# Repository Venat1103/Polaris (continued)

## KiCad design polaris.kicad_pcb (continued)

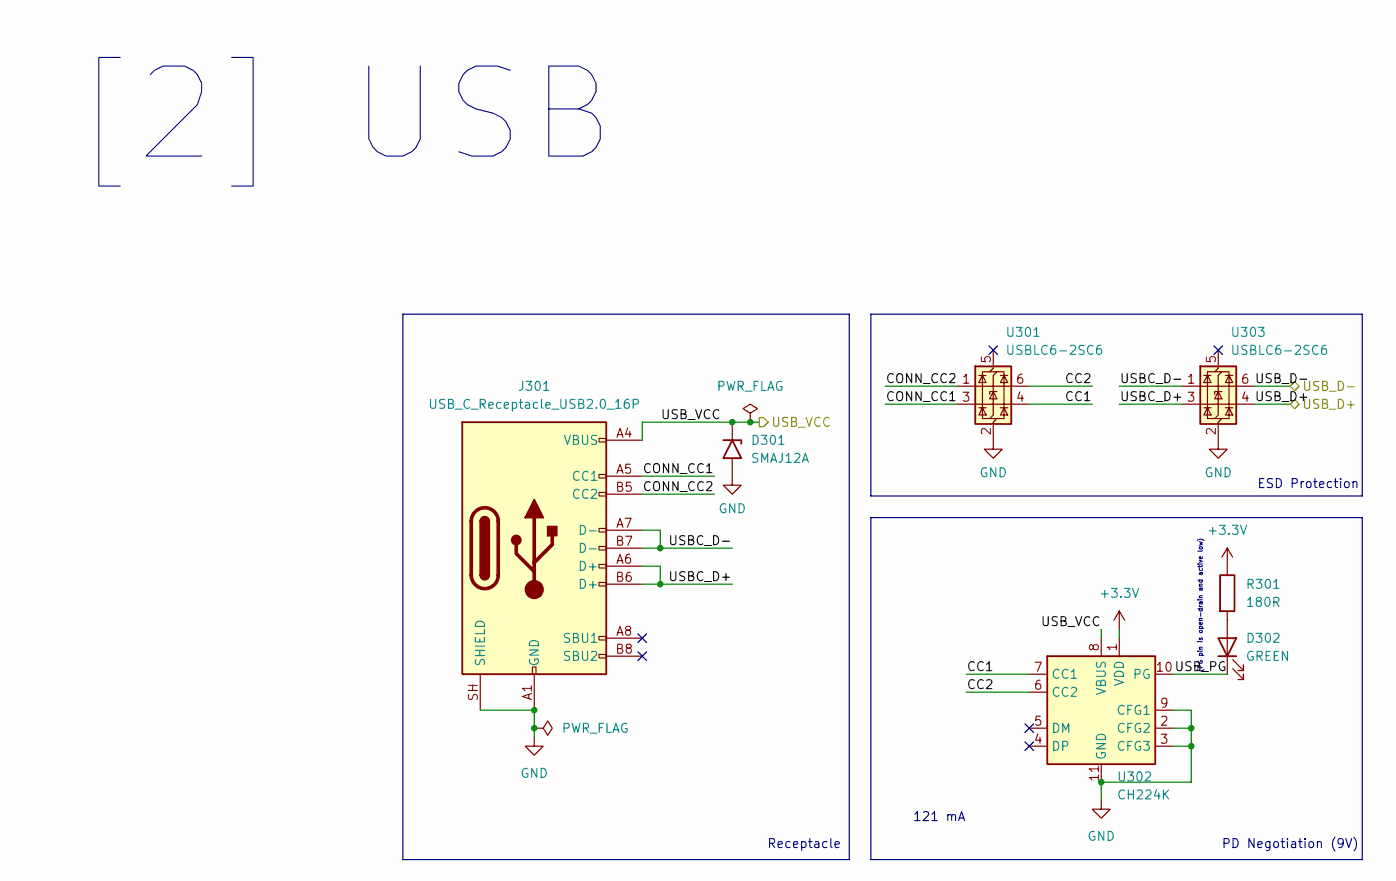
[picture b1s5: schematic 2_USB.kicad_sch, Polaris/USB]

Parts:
D301: SMAJ12A; D_SMA
D302: GREEN; LED_0603_1608Metric
J301: USB_C_Receptacle_USB2.0_16P; USB_C_Receptacle_HRO_TYPE-C-31-M-12
R301: 180R; R_0603_1608Metric
U301, U303: USBLC6-2SC6; SOT-23-6
U302: CH224K; SSOP-10-1EP_3.9x4.9mm_P1mm_EP2.1x3.3mm

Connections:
+3.3V: R301.1, U302.1 (VDD); also elsewhere on the board
/1_Power/USB_VCC: D301.1 (A1), J301.A4 (VBUS), J301.A9 (VBUS), J301.B4 (VBUS), J301.B9 (VBUS), U302.8 (VBUS); also elsewhere on the board
/2_USB/CC1: U301.4 (I/O2), U302.7 (CC1)
/2_USB/CC2: U301.6 (I/O1), U302.6 (CC2)
/2_USB/CONN_CC1: J301.A5 (CC1), U301.3 (I/O2)
/2_USB/CONN_CC2: J301.B5 (CC2), U301.1 (I/O1)
/2_USB/USBC_D+: J301.A6 (D+), J301.B6 (D+), U303.3 (I/O2)
/2_USB/USBC_D-: J301.A7 (D-), J301.B7 (D-), U303.1 (I/O1)
/2_USB/USB_D+: U303.4 (I/O2); also elsewhere on the board
/2_USB/USB_D-: U303.6 (I/O1); also elsewhere on the board
/2_USB/USB_PG: D302.1 (K), U302.10 (PG)
GND: D301.2 (A2), J301.A1 (GND), J301.A12 (GND), J301.B1 (GND), J301.B12 (GND), J301.SH (SHIELD), U301.2 (GND), U302.2 (CFG2), U302.3 (CFG3), U302.9 (CFG1), U302.11 (GND), U303.2 (GND); also elsewhere on the board
unnamed: D302.2 (A), R301.2

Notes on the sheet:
(PG pin is open-drain and active low)
Receptacle
[2] USB
121 mA
ESD Protection
PD Negotiation (9V)

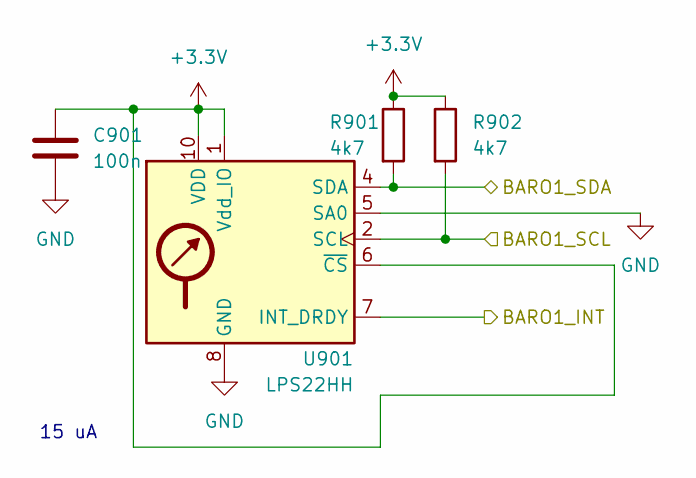
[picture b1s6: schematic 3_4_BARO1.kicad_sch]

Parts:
C901: 100n; C_0603_1608Metric
R901, R902: 4k7; R_0603_1608Metric
U901: LPS22HH; ST_HLGA-10_2x2mm_P0.5mm_LayoutBorder3x2y

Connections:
+3.3V: C901.2, R901.1, R902.1, U901.1 (Vdd_IO), U901.6 (~CS), U901.10 (VDD); also elsewhere on the board
/3_NavigationProcessor/LPS_INT: U901.7 (INT_DRDY); also elsewhere on the board
/3_NavigationProcessor/LPS_SCL: R902.2, U901.2 (SCL); also elsewhere on the board
/3_NavigationProcessor/LPS_SDA: R901.2, U901.4 (SDA); also elsewhere on the board
GND: C901.1, U901.3 (GND), U901.5 (SA0), U901.8 (GND), U901.9 (GND); also elsewhere on the board

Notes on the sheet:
15 uA

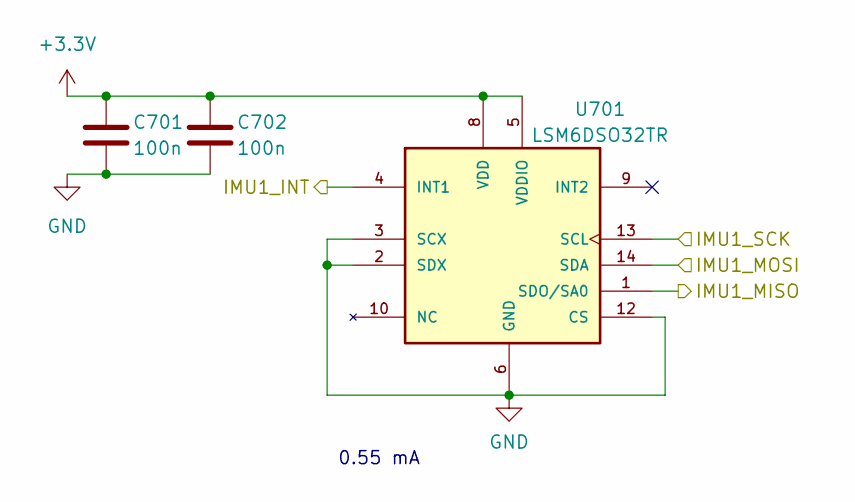
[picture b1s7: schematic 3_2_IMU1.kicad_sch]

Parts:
C701, C702: 100n; C_0603_1608Metric
U701: LSM6DSO32TR

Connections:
+3.3V: C701.1, C702.1, U701.5 (VDDIO), U701.8 (VDD); also elsewhere on the board
/3_NavigationProcessor/LSM_INT: U701.4 (INT1); also elsewhere on the board
/3_NavigationProcessor/LSM_MISO: U701.1 (SDO/SA0); also elsewhere on the board
/3_NavigationProcessor/LSM_MOSI: U701.14 (SDA); also elsewhere on the board
/3_NavigationProcessor/LSM_SCK: U701.13 (SCL); also elsewhere on the board
GND: C701.2, C702.2, U701.2 (SDX), U701.3 (SCX), U701.6 (GND), U701.7 (GND), U701.12 (CS); also elsewhere on the board

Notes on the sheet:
0.55 mA

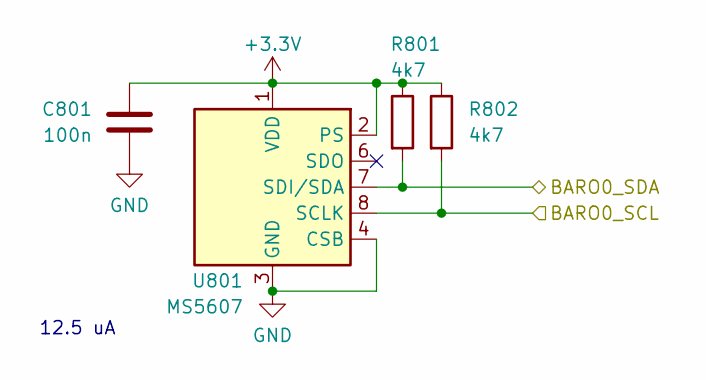
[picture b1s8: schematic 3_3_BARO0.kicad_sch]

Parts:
C801: 100n; C_0603_1608Metric
R801, R802: 4k7; R_0603_1608Metric
U801: MS5607; LGA-8_3x5mm_P1.25mm

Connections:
+3.3V: C801.1, R801.1, R802.1, U801.1 (VDD), U801.2 (PS); also elsewhere on the board
/3_NavigationProcessor/MS_SCL: R802.2, U801.8 (SCLK); also elsewhere on the board
/3_NavigationProcessor/MS_SDA: R801.2, U801.7 (SDI/SDA); also elsewhere on the board
GND: C801.2, U801.3 (GND), U801.4 (CSB), U801.5 (CSB); also elsewhere on the board

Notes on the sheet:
12.5 uA

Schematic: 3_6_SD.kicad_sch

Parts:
C1101: 10u; C_0805_2012Metric
C1102: 100n; C_0603_1608Metric
U1101: THD-2528-11SD-GF; TF-SMD_THD2528-11SD-GF

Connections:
+3.3V: C1101.1, C1102.1, U1101.4 (VDD); also elsewhere on the board
/3_NavigationProcessor/SD_CD: U1101.9 (CD); also elsewhere on the board
/3_NavigationProcessor/SD_CLK: U1101.5 (CLK); also elsewhere on the board
/3_NavigationProcessor/SD_CMD: U1101.3 (CMD); also elsewhere on the board
/3_NavigationProcessor/SD_DAT0: U1101.7 (DAT0); also elsewhere on the board
/3_NavigationProcessor/SD_DAT1: U1101.8 (DAT1); also elsewhere on the board
/3_NavigationProcessor/SD_DAT2: U1101.1 (DAT2); also elsewhere on the board
/3_NavigationProcessor/SD_DAT3: U1101.2 (DAT3); also elsewhere on the board
GND: C1101.2, C1102.2, U1101.6 (VSS), U1101.10 (SHELL), U1101.11 (SHELL), U1101.12 (SHELL), U1101.13 (SHELL); also elsewhere on the board

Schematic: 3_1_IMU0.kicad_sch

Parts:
C601: 2u2; C_0603_1608Metric
C602: 100n; C_0603_1608Metric
C603: 10n; C_0603_1608Metric
U601: ICM-42688-P

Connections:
+3.3V: C601.1, C602.1, C603.1, U601.5 (VDDIO), U601.8 (VDD); also elsewhere on the board
/3_NavigationProcessor/ICM_CS: U601.12 (AP_CS); also elsewhere on the board
/3_NavigationProcessor/ICM_INT: U601.4 (INT1); also elsewhere on the board
/3_NavigationProcessor/ICM_MISO: U601.1 (AP_SDO); also elsewhere on the board
/3_NavigationProcessor/ICM_MOSI: U601.14 (AP_SDA); also elsewhere on the board
/3_NavigationProcessor/ICM_SCK: U601.13 (AP_SCL); also elsewhere on the board
GND: C601.2, C602.2, C603.2, U601.2 (RESV_2), U601.3 (RESV_3), U601.6 (GND), U601.7 (RESV_7), U601.10 (RESV_10), U601.11 (RESV_11); also elsewhere on the board

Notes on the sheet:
0.88 mA

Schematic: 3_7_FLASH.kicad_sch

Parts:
C1201: 100n; C_0603_1608Metric
U1201: W25Q128JVS; SOIC-8_5.3x5.3mm_P1.27mm

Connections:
+3.3V: C1201.1, U1201.8 (VCC); also elsewhere on the board
/3_NavigationProcessor/FLASH_CLK: U1201.6 (CLK); also elsewhere on the board
/3_NavigationProcessor/FLASH_CS: U1201.1 (~CS); also elsewhere on the board
/3_NavigationProcessor/FLASH_IO0: U1201.5 (DI/IO_{0}); also elsewhere on the board
/3_NavigationProcessor/FLASH_IO1: U1201.2 (DO/IO_{1}); also elsewhere on the board
/3_NavigationProcessor/FLASH_IO2: U1201.3 (~WP/IO_{2}); also elsewhere on the board
/3_NavigationProcessor/FLASH_IO3: U1201.7 (~HOLD/~RESET/IO_{3}); also elsewhere on the board
GND: C1201.2, U1201.4 (GND); also elsewhere on the board

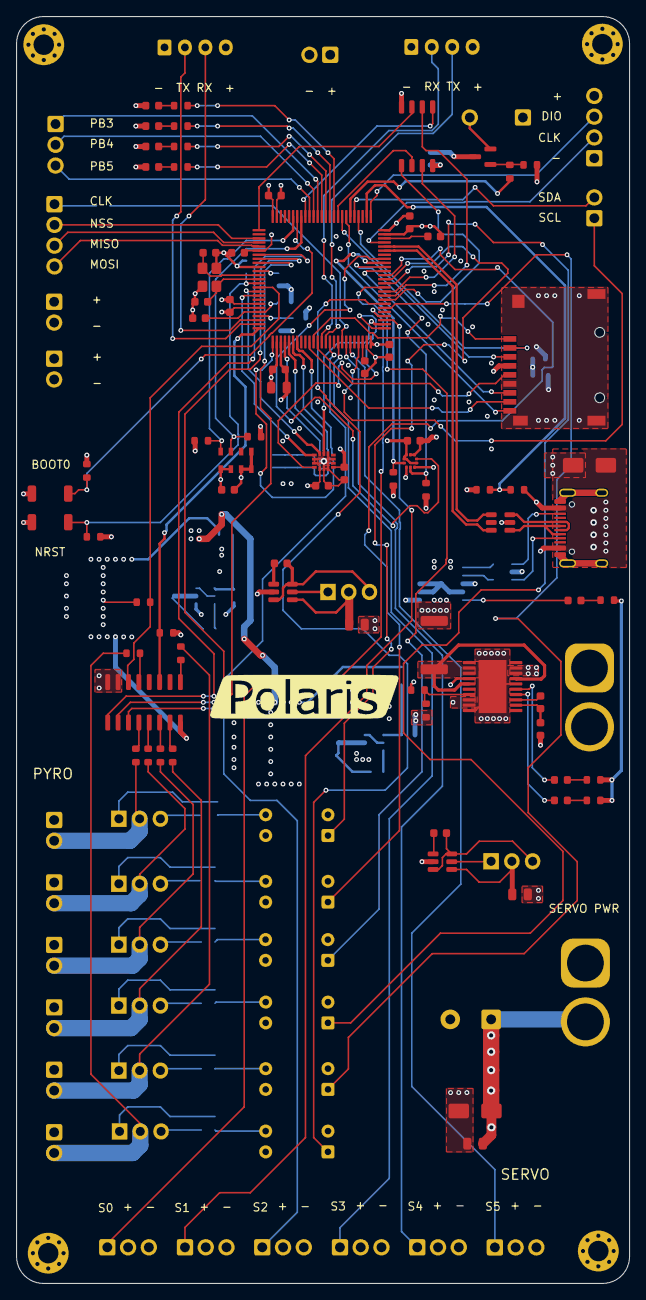
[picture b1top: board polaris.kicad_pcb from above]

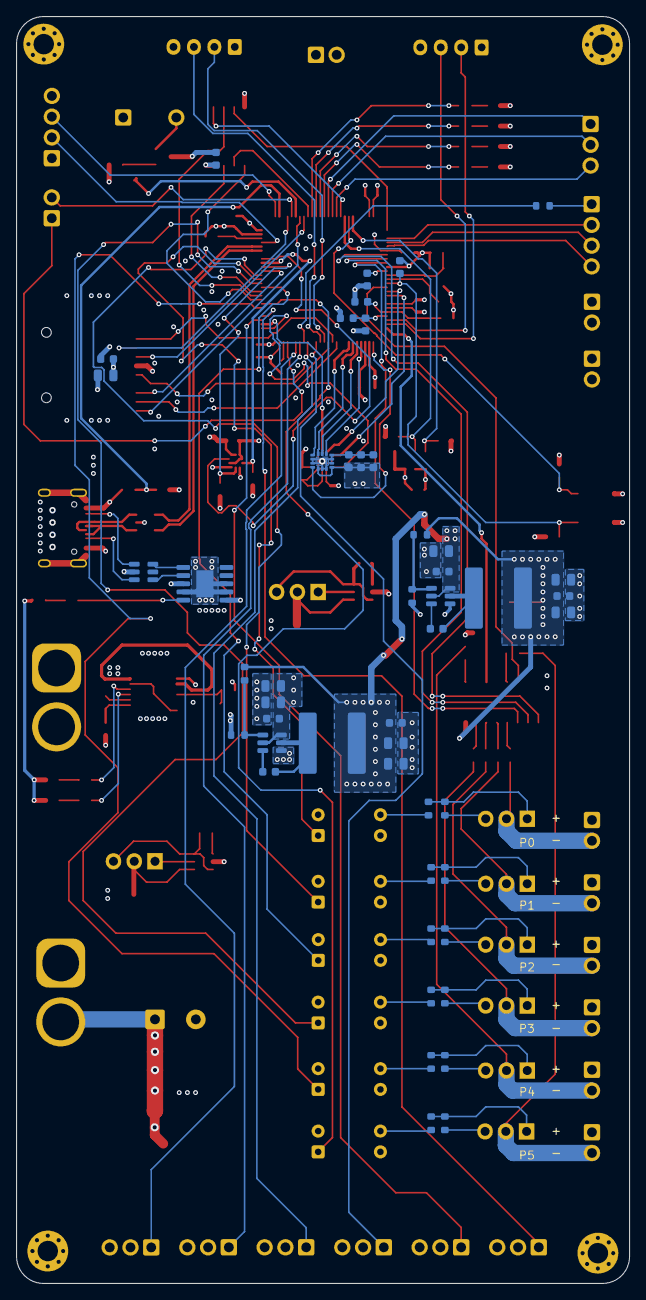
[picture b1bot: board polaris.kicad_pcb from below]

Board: 4 copper layers, 75.0 x 155.0 mm, 167 parts (49 on the bottom side), 138 nets.

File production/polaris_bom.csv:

Designator,Footprint,Quantity,Value,LCSC Part #
BZ401,AC1255,1,AC2208,
"C1101, C207, C208, C209, C211, C214, C217, C218",0805,8,10u,
"C1102, C1201, C203, C204, C210, C212, C213, C215, C216, C219, C404, C405, C409, C410, C411, C412, C413, C414, C415, C416, C602, C701, C702, C801, C901",0603,25,100n,
C201,0603,1,0u22,
C202,0603,1,10p,
"C205, C206, C408, C502",0805,4,4u7,
"C401, C402",0603,2,20p,
C403,0603,1,1u,
"C406, C407, C601",0603,3,2u2,
C501,CP_Radial_D13.0mm_P5.00mm,1,2200u,
C603,0603,1,10n,
"D201, D302, D401, D402, D403, D404",0603,6,GREEN,
D202,0603,1,ORANGE,
D301,D_SMA,1,SMAJ12A,
D501,D_SMA,1,SMAJ9.0CA,
FB402,0603,1,FerriteBead,
"J101, J501",AMASS_XT60-F_1x02_P7.20mm_Vertical,2,XT60-M,
J102,TerminalBlock_Xinya_XY308-2.54-4P_1x04_P2.54mm_Horizontal,1,SPI,
J103,TerminalBlock_Xinya_XY308-2.54-2P_1x02_P2.54mm_Horizontal,1,I2C,
J104,TerminalBlock_Xinya_XY308-2.54-3P_1x03_P2.54mm_Horizontal,1,PB,
J105,TerminalBlock_Xinya_XY308-2.54-4P_1x04_P2.54mm_Horizontal,1,SWD,
J106,TerminalBlock_Xinya_XY308-2.54-2P_1x02_P2.54mm_Horizontal,1,PYRO0,
J107,TerminalBlock_Xinya_XY308-2.54-2P_1x02_P2.54mm_Horizontal,1,PYRO1,
J108,TerminalBlock_Xinya_XY308-2.54-2P_1x02_P2.54mm_Horizontal,1,PYRO2,
J109,TerminalBlock_Xinya_XY308-2.54-2P_1x02_P2.54mm_Horizontal,1,PYRO3,
J110,TerminalBlock_Xinya_XY308-2.54-2P_1x02_P2.54mm_Horizontal,1,PYRO4,
J111,TerminalBlock_Xinya_XY308-2.54-2P_1x02_P2.54mm_Horizontal,1,PYRO5,
J112,TerminalBlock_Xinya_XY308-2.54-3P_1x03_P2.54mm_Horizontal,1,SERVO0,
J113,TerminalBlock_Xinya_XY308-2.54-3P_1x03_P2.54mm_Horizontal,1,SERVO1,
J114,TerminalBlock_Xinya_XY308-2.54-3P_1x03_P2.54mm_Horizontal,1,SERVO2,
J115,TerminalBlock_Xinya_XY308-2.54-3P_1x03_P2.54mm_Horizontal,1,SERVO3,
J116,TerminalBlock_Xinya_XY308-2.54-3P_1x03_P2.54mm_Horizontal,1,SERVO4,
J117,TerminalBlock_Xinya_XY308-2.54-3P_1x03_P2.54mm_Horizontal,1,SERVO5,
J118,JST_XH_B4B-XH-A_1x04_P2.50mm_Vertical,1,RADIO,
"J119, J121, J122",TerminalBlock_Xinya_XY308-2.54-2P_1x02_P2.54mm_Horizontal,3,POWER,
J120,JST_XH_B4B-XH-A_1x04_P2.50mm_Vertical,1,GNSS,
J301,USB_C_Receptacle_HRO_TYPE-C-31-M-12,1,USB_C_Receptacle_USB2.0_16P,
"L201, L202",L_Sunlord_SWPA8040S,2,10u,
"Q201, Q202, Q501, Q502, Q503, Q504, Q505, Q506",TO-220-3_Vertical,8,IRLZ44N,
Q401,SOT-23,1,Q_NMOS,
R101,0603,1,0R,
R201,0603,1,360k,
"R202, R407",0603,2,47k,
R203,2512,1,0R1,
"R204, R205, R301, R404, R405, R408, R409",0603,7,180R,
R206,0603,1,162k,
"R207, R209",0603,2,22.1k,
"R208, R403",0603,2,100k,
"R401, R402, R503, R504, R505, R506, R507, R511, R512, R513, R514, R517, R518, R519, R520, R801, R802, R901, R902",0603,19,4k7,
"R406, R501, R502, R509, R510, R515, R516",0603,7,47R,
R410,0603,1,22k1,
R508,0603,1,1k,
"SW401, SW402",SW_SPST_TS-1088-xR020,2,SW_Push,
U1101,TF-SMD_THD2528-11SD-GF,1,THD-2528-11SD-GF,
U1201,SOIC-8_5.3x5.3mm_P1.27mm,1,W25Q128JVS,
U201,HTSSOP-20-1EP_4.4x6.5mm_P0.65mm_EP3.4x6.5mm_Mask2.4x3.7mm,1,BQ24005,
"U202, U203",SOT-23-6,2,LM74700,
"U204, U205",SOT-23-6,2,LMR51430,
"U301, U303",SOT-23-6,2,USBLC6-2SC6,
U302,SSOP-10-1EP_3.9x4.9mm_P1mm_EP2.1x3.3mm,1,CH224K,
U401,LQFP-100_14x14mm_P0.5mm,1,STM32F446VETx,
"U501, U502, U504, U505, U506, U507",DIP-4_W7.62mm,6,PC817,
U503,SOIC-16_3.9x9.9mm_P1.27mm,1,CD4051B,
U601,ICM-42688-P,1,ICM-42688-P,
U701,LSM6DSO32TR,1,LSM6DSO32TR,
U801,LGA-8_3x5mm_P1.25mm,1,MS5607,
U901,LPS22HH,1,LPS22HH,
Y401,Crystal_SMD_3225-4Pin_3.2x2.5mm,1,YXC YSX321SL,

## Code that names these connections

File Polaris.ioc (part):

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Mcu.Name=STM32F446V(C-E)Tx
Mcu.Package=LQFP100
Mcu.UserName=STM32F446VETx
PA0-WKUP.Mode=Asynchronous
PA0-WKUP.Signal=UART4_TX
PA1.Mode=Asynchronous
PA1.Signal=UART4_RX
PA11.Mode=Device_Only
PA11.Signal=USB_OTG_FS_DM
PA12.Mode=Device_Only
PA12.Signal=USB_OTG_FS_DP
PA13.Mode=Serial_Wire
PA13.Signal=SYS_JTMS-SWDIO
PA14.Mode=Serial_Wire
PA14.Signal=SYS_JTCK-SWCLK
PA2.GPIOParameters=GPIO_Label
PA2.GPIO_Label=PYRO_SENSE
PA2.Signal=GPIO_Analog
PA3.GPIOParameters=GPIO_Label
PA3.GPIO_Label=ICM_INT
PA3.Signal=GPXTI3
PA4.Mode=NSS_Signal_Hard_Output
PA4.Signal=SPI1_NSS
PA5.Mode=Full_Duplex_Master
PA5.Signal=SPI1_SCK
PA6.Mode=Full_Duplex_Master
PA6.Signal=SPI1_MISO
PA7.Mode=Full_Duplex_Master
PA7.Signal=SPI1_MOSI
PA8.Mode=I2C
PA8.Signal=I2C3_SCL
PA9.GPIOParameters=GPIO_Label
PA9.GPIO_Label=LPS_INT
PA9.Signal=GPXTI9
PB0.Mode=SD_4_bits_Wide_bus
PB0.Signal=SDIO_D1
PB1.Mode=SD_4_bits_Wide_bus
PB1.Signal=SDIO_D2
PB10.Mode=I2C
PB10.Signal=I2C2_SCL
PB12.GPIOParameters=GPIO_Label
PB12.GPIO_Label=LSM_INT
PB12.Signal=GPXTI12
PB13.Mode=Full_Duplex_Master
PB13.Signal=SPI2_SCK
PB14.GPIOParameters=GPIO_Label
PB14.GPIO_Label=Servo0
PB14.Signal=S_TIM12_CH1
PB15.GPIOParameters=GPIO_Label
PB15.GPIO_Label=Servo1
PB15.Signal=S_TIM12_CH2
PB2.Mode=SD_4_bits_Wide_bus
PB2.Signal=SDIO_CK
PB3.GPIOParameters=GPIO_Label
PB3.GPIO_Label=PB3
PB3.Signal=GPIO_Input
PB4.GPIOParameters=GPIO_Label
PB4.GPIO_Label=PB4
PB4.Signal=GPIO_Input
PB5.GPIOParameters=GPIO_Label
PB5.GPIO_Label=PB5
PB5.Signal=GPIO_Input
PB6.Mode=Single Bank 1
PB6.Signal=QUADSPI_BK1_NCS
PB7.Mode=I2C
PB7.Signal=I2C1_SDA
PB8.Mode=I2C
PB8.Signal=I2C1_SCL
PC0.GPIOParameters=GPIO_PuPd,GPIO_Label,GPIO_ModeDefaultOutputPP
PC0.GPIO_Label=MUX_EN
PC0.GPIO_ModeDefaultOutputPP=GPIO_MODE_OUTPUT_OD
PC0.GPIO_PuPd=GPIO_NOPULL
PC0.Signal=GPIO_Output
PC1.Mode=Full_Duplex_Master
PC1.Signal=SPI2_MOSI
PC11.Mode=SD_4_bits_Wide_bus
PC11.Signal=SDIO_D3
PC12.Mode=I2C
PC12.Signal=I2C2_SDA
PC13.GPIOParameters=GPIO_Label
PC13.GPIO_Label=MUX_A
PC13.Signal=GPIO_Output
PC14-OSC32_IN.GPIOParameters=GPIO_Label
PC14-OSC32_IN.GPIO_Label=MUX_B
PC14-OSC32_IN.Signal=GPIO_Output
PC15-OSC32_OUT.GPIOParameters=GPIO_Label
PC15-OSC32_OUT.GPIO_Label=MUX_C
PC15-OSC32_OUT.Signal=GPIO_Output
PC2.Mode=Full_Duplex_Master
PC2.Signal=SPI2_MISO
PC6.GPIOParameters=GPIO_Label
PC6.GPIO_Label=Fire0
PC6.Signal=GPIO_Output
PC7.GPIOParameters=GPIO_Label
PC7.GPIO_Label=Fire1
PC7.Signal=GPIO_Output
PC8.Mode=SD_4_bits_Wide_bus
PC8.Signal=SDIO_D0
PC9.Mode=I2C
PC9.Signal=I2C3_SDA
PD0.GPIOParameters=GPIO_Label
PD0.GPIO_Label=BUZZER
PD0.Signal=GPIO_Output
PD1.GPIOParameters=GPIO_Label
PD1.GPIO_Label=SD_CD
PD1.Signal=GPIO_Input
PD10.GPIOParameters=GPIO_Label
PD10.GPIO_Label=Main1
PD10.Signal=GPIO_Output
PD11.Mode=Single Bank 1
PD11.Signal=QUADSPI_BK1_IO0
PD12.Mode=Single Bank 1
PD12.Signal=QUADSPI_BK1_IO1
PD13.Mode=Single Bank 1
PD13.Signal=QUADSPI_BK1_IO3
PD14.GPIOParameters=GPIO_Label
PD14.GPIO_Label=Drogue0
PD14.Signal=GPIO_Output
PD15.GPIOParameters=GPIO_Label
PD15.GPIO_Label=Drogue1
PD15.Signal=GPIO_Output
PD2.Mode=SD_4_bits_Wide_bus
PD2.Signal=SDIO_CMD
PD3.Mode=Single Bank 1
PD3.Signal=QUADSPI_CLK
PD4.GPIOParameters=GPIO_Label
PD4.GPIO_Label=STAT1
PD4.Signal=GPIO_Output
PD5.GPIOParameters=GPIO_Label
PD5.GPIO_Label=STAT2
PD5.Signal=GPIO_Output
PD6.GPIOParameters=GPIO_Label
PD6.GPIO_Label=STAT3
PD6.Signal=GPIO_Output
PD7.GPIOParameters=GPIO_Label
PD7.GPIO_Label=STAT4
PD7.Signal=GPIO_Output
PD9.GPIOParameters=GPIO_Label
PD9.GPIO_Label=Main0
PD9.Signal=GPIO_Output
PE11.GPIOParameters=GPIO_Label
PE11.GPIO_Label=Servo3
PE11.Signal=S_TIM1_CH2
PE12.Mode=Full_Duplex_Master
PE12.Signal=SPI4_SCK
PE13.GPIOParameters=GPIO_Label
PE13.GPIO_Label=Servo4
PE13.Signal=S_TIM1_CH3
PE14.GPIOParameters=GPIO_Label
PE14.GPIO_Label=Servo5
PE14.Signal=S_TIM1_CH4
PE2.Mode=Single Bank 1
PE2.Signal=QUADSPI_BK1_IO2
PE4.Mode=NSS_Signal_Hard_Output
PE4.Signal=SPI4_NSS
PE5.Mode=Full_Duplex_Master
PE5.Signal=SPI4_MISO
PE6.Mode=Full_Duplex_Master
PE6.Signal=SPI4_MOSI
PE7.Mode=Asynchronous
PE7.Signal=UART5_RX
PE8.Mode=Asynchronous
PE8.Signal=UART5_TX
PE9.GPIOParameters=GPIO_Label
PE9.GPIO_Label=Servo2
PE9.Signal=S_TIM1_CH1
PH0-OSC_IN.Mode=HSE-External-Oscillator
PH0-OSC_IN.Signal=RCC_OSC_IN
PH1-OSC_OUT.Mode=HSE-External-Oscillator
PH1-OSC_OUT.Signal=RCC_OSC_OUT
RCC.HSE_VALUE=12000000
board=custom

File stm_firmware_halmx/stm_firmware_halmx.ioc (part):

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Mcu.Name=STM32F446V(C-E)Tx
Mcu.Package=LQFP100
Mcu.UserName=STM32F446VETx
PA0-WKUP.GPIOParameters=GPIO_Label
PA0-WKUP.GPIO_Label=GNSS_TX
PA0-WKUP.Mode=Asynchronous
PA0-WKUP.Signal=UART4_TX
PA1.GPIOParameters=GPIO_Label
PA1.GPIO_Label=GNSS_RX
PA1.Mode=Asynchronous
PA1.Signal=UART4_RX
PA11.Mode=Device_Only
PA11.Signal=USB_OTG_FS_DM
PA12.Mode=Device_Only
PA12.Signal=USB_OTG_FS_DP
PA13.Mode=Serial_Wire
PA13.Signal=SYS_JTMS-SWDIO
PA14.Mode=Serial_Wire
PA14.Signal=SYS_JTCK-SWCLK
PA2.GPIOParameters=GPIO_Label
PA2.GPIO_Label=PYRO_SENSE
PA2.Signal=SharedAnalog_PA2
PA3.GPIOParameters=GPIO_Label,GPIO_ModeDefaultEXTI
PA3.GPIO_Label=IMU0_ICM_INT
PA3.GPIO_ModeDefaultEXTI=GPIO_MODE_IT_FALLING
PA3.Signal=GPXTI3
PA4.GPIOParameters=GPIO_Label
PA4.GPIO_Label=IMU0_ICM_NSS
PA4.Mode=NSS_Signal_Hard_Output
PA4.Signal=SPI1_NSS
PA5.GPIOParameters=GPIO_Label
PA5.GPIO_Label=IMU0_ICM_SCK
PA5.Mode=Full_Duplex_Master
PA5.Signal=SPI1_SCK
PA6.GPIOParameters=GPIO_Label
PA6.GPIO_Label=IMU0_ICM_MISO
PA6.Mode=Full_Duplex_Master
PA6.Signal=SPI1_MISO
PA7.GPIOParameters=GPIO_Label
PA7.GPIO_Label=IMU0_ICM_MOSI
PA7.Mode=Full_Duplex_Master
PA7.Signal=SPI1_MOSI
PA8.GPIOParameters=GPIO_Label
PA8.GPIO_Label=BARO1_LPS_SCL
PA8.Mode=I2C
PA8.Signal=I2C3_SCL
PA9.GPIOParameters=GPIO_Label,GPIO_ModeDefaultEXTI
PA9.GPIO_Label=BARO1_LPS_INT
PA9.GPIO_ModeDefaultEXTI=GPIO_MODE_IT_RISING
PA9.Signal=GPXTI9
PB0.Mode=SD_4_bits_Wide_bus
PB0.Signal=SDIO_D1
PB1.Mode=SD_4_bits_Wide_bus
PB1.Signal=SDIO_D2
PB12.GPIOParameters=GPIO_Label,GPIO_ModeDefaultEXTI
PB12.GPIO_Label=IMU1_LSM_INT
PB12.GPIO_ModeDefaultEXTI=GPIO_MODE_IT_RISING
PB12.Signal=GPXTI12
PB13.GPIOParameters=GPIO_Label
PB13.GPIO_Label=IMU1_LSM_SCK
PB13.Mode=Full_Duplex_Master
PB13.Signal=SPI2_SCK
PB14.GPIOParameters=GPIO_Label
PB14.GPIO_Label=SERVO_0
PB14.Signal=S_TIM12_CH1
PB15.GPIOParameters=GPIO_Label
PB15.GPIO_Label=SERVO_1
PB15.Signal=S_TIM12_CH2
PB2.Mode=SD_4_bits_Wide_bus
PB2.Signal=SDIO_CK
PB3.GPIOParameters=GPIO_Label
PB3.GPIO_Label=PB3
PB3.Signal=GPIO_Input
PB4.GPIOParameters=GPIO_Label
PB4.GPIO_Label=PB4
PB4.Signal=GPIO_Input
PB5.GPIOParameters=GPIO_Label
PB5.GPIO_Label=PB5
PB5.Signal=GPIO_Input
PB6.Mode=Single Bank 1
PB6.Signal=QUADSPI_BK1_NCS
PB7.GPIOParameters=GPIO_Label
PB7.GPIO_Label=BARO0_MS_SDA
PB7.Mode=I2C
PB7.Signal=I2C1_SDA
PB8.GPIOParameters=GPIO_Label
PB8.GPIO_Label=BARO0_MS_SCL
PB8.Mode=I2C
PB8.Signal=I2C1_SCL
PC0.GPIOParameters=GPIO_PuPd,GPIO_Label,GPIO_ModeDefaultOutputPP
PC0.GPIO_Label=MUX_EN
PC0.GPIO_ModeDefaultOutputPP=GPIO_MODE_OUTPUT_OD
PC0.GPIO_PuPd=GPIO_NOPULL
PC0.Signal=GPIO_Output
PC11.Mode=SD_4_bits_Wide_bus
PC11.Signal=SDIO_D3
PC13.GPIOParameters=GPIO_Label
PC13.GPIO_Label=MUX_BIT_A
PC13.Signal=GPIO_Output
PC14-OSC32_IN.GPIOParameters=GPIO_Label
PC14-OSC32_IN.GPIO_Label=MUX_BIT_B
PC14-OSC32_IN.Signal=GPIO_Output
PC15-OSC32_OUT.GPIOParameters=GPIO_Label
PC15-OSC32_OUT.GPIO_Label=MUX_BIT_C
PC15-OSC32_OUT.Signal=GPIO_Output
PC2.GPIOParameters=GPIO_Label
PC2.GPIO_Label=IMU1_LSM_MISO
PC2.Mode=Full_Duplex_Master
PC2.Signal=SPI2_MISO
PC3.GPIOParameters=GPIO_Label
PC3.GPIO_Label=IMU1_LSM_MOSI
PC3.Mode=Full_Duplex_Master
PC3.Signal=SPI2_MOSI
PC6.GPIOParameters=GPIO_Label
PC6.GPIO_Label=IGNITER_0
PC6.Signal=GPIO_Output
PC7.GPIOParameters=GPIO_Label
PC7.GPIO_Label=IGNITER_1
PC7.Signal=GPIO_Output
PC8.Mode=SD_4_bits_Wide_bus
PC8.Signal=SDIO_D0
PC9.GPIOParameters=GPIO_Label
PC9.GPIO_Label=BARO1_LPS_SDA
PC9.Mode=I2C
PC9.Signal=I2C3_SDA
PD0.GPIOParameters=GPIO_Label
PD0.GPIO_Label=BUZZER
PD0.Signal=GPIO_Output
PD1.GPIOParameters=GPIO_Label
PD1.GPIO_Label=SD_CD
PD1.Signal=GPIO_Input
PD10.GPIOParameters=GPIO_Label
PD10.GPIO_Label=MAIN_PYRO_1
PD10.Signal=GPIO_Output
PD11.Mode=Single Bank 1
PD11.Signal=QUADSPI_BK1_IO0
PD12.Mode=Single Bank 1
PD12.Signal=QUADSPI_BK1_IO1
PD13.Mode=Single Bank 1
PD13.Signal=QUADSPI_BK1_IO3
PD14.GPIOParameters=GPIO_Label
PD14.GPIO_Label=DROGUE_PYRO_0
PD14.Signal=GPIO_Output
PD15.GPIOParameters=GPIO_Label
PD15.GPIO_Label=DROGUE_PYRO_1
PD15.Signal=GPIO_Output
PD2.Mode=SD_4_bits_Wide_bus
PD2.Signal=SDIO_CMD
PD3.Mode=Single Bank 1
PD3.Signal=QUADSPI_CLK
PD4.GPIOParameters=GPIO_Label
PD4.GPIO_Label=STAT_LED_0
PD4.Signal=GPIO_Output
PD5.GPIOParameters=GPIO_Label
PD5.GPIO_Label=STAT_LED_1
PD5.Signal=GPIO_Output
PD6.GPIOParameters=GPIO_Label
PD6.GPIO_Label=STAT_LED_2
PD6.Signal=GPIO_Output
PD7.GPIOParameters=GPIO_Label
PD7.GPIO_Label=STAT_LED_3
PD7.Signal=GPIO_Output
PD9.GPIOParameters=GPIO_Label
PD9.GPIO_Label=MAIN_PYRO_0
PD9.Signal=GPIO_Output
PE11.GPIOParameters=GPIO_Label
PE11.GPIO_Label=SERVO_3
PE11.Signal=S_TIM1_CH2
PE13.GPIOParameters=GPIO_Label
PE13.GPIO_Label=SERVO_4
PE13.Signal=S_TIM1_CH3
PE14.GPIOParameters=GPIO_Label
PE14.GPIO_Label=SERVO_5
PE14.Signal=S_TIM1_CH4
PE2.Mode=Single Bank 1
PE2.Signal=QUADSPI_BK1_IO2
PE7.GPIOParameters=GPIO_Label
PE7.GPIO_Label=RF_RX
PE7.Mode=Asynchronous
PE7.Signal=UART5_RX
PE8.GPIOParameters=GPIO_Label
PE8.GPIO_Label=RF_TX
PE8.Mode=Asynchronous
PE8.Signal=UART5_TX
PE9.GPIOParameters=GPIO_Label
PE9.GPIO_Label=SERVO_2
PE9.Signal=S_TIM1_CH1
PH0-OSC_IN.Mode=HSE-External-Oscillator
PH0-OSC_IN.Signal=RCC_OSC_IN
PH1-OSC_OUT.Mode=HSE-External-Oscillator
PH1-OSC_OUT.Signal=RCC_OSC_OUT
RCC.HSE_VALUE=12000000
board=custom

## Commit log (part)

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2026-06-13 Added symbols and footprints Changed schematic to use footprints and symbols from added symbols and footprints
2026-06-14 Changed oscillator series resistors to DNP
2026-06-14 Added switching regulator notes
2026-06-14 Added status LEDs and buzzer for indication
2026-06-14 Added status LEDs for TLM (forgot to add previously)
2026-06-14 Redid ESD protection because the previous chip couldn't handle 9V from USB-PD Finished status indication sections
2026-06-14 Redid LoRa radio section Changed regulator output inductor to 10 uH based on availability
2026-06-14 Added system architecture to readme Modified regulator inductor Added test points to LoRa radio
2026-06-14 More uploads
2026-06-15 Corrected power section calculations Added Polaris system architecture to README
2026-06-15 Updated system architecture diagram
2026-06-15 Used a different microSD card slot symbol (The old one loooked bad)
2026-06-15 Create CubeIDE Project
2026-06-15 Corrected power section for the billionth time Added programming notes
2026-06-16 Added Title Block
2026-06-16 Added hardware switch for active control Also added a coupling capacitor between receptacle shells and reference ground Added some more notes
2026-06-16 Added backup files to gitignore
2026-06-16 Corrected grounding of shield pins in receptacles Also changed SHELL pin of microSD slot to Passive
2026-06-17 Added TVS diode to servo power line
2026-06-17 Broke out remaining GPIO pins of NAV
2026-06-17 Used custom buzzer footprint because why not
2026-06-17 Added more notes and finished footprint assignment
2026-06-17 Updated backup
2026-06-17 Broke out the remaining GPIO pins of NAV
2026-06-17 Finally started the PCB layout and routing Only took me a few decades Also labeled some unlabeled nets in the schematic Changed the USB mux to be two 1x3 pin headers instead of one 2x3 Edited symbols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
2026-06-17 Made an extremely suboptimal ESD protection connection for USB
2026-06-17 fsm architecture
2026-06-18 fsm implementation
2026-06-18 Add option for chamber pressure, remove current, voltage readings
2026-06-18 Renamed a few nets
2026-06-18 Continued work on PCB layout
2026-06-20 Better teminology
2026-06-20 Continued ESD and USB-C section of PCB
    Changed ESD device to one more suitable, previously thought unavailable
    Started basic component placement
2026-06-20 Delete polaris.kicad_dru
    Not needed
2026-06-21 Redesigned the whole thing for the hundredth time
    Changed from dual MCU to single MCU
    Changed main MCU to STM32F446VE
    Added CubeMX project (ioc) file for easy access to pinouts
    Note: The PCB file still contains the previous connections and footprints
2026-06-21 change microcontroller and remove telemetry processor
2026-06-22 initiate com port logging and code restructuring/relabelling
2026-06-22 Switched main 3.3V LDO to a modern part
    New one: TLV75733
    Old one: NCP1117
    New one has cleaner output, lower dropout voltage and is cheaper.
    Also continued completing the connections for NAV
    Updated README to include changes to architecture
    Also updated pin connections on CubeMX (ioc) file
2026-06-23 Continued connections for the new NAV
    Added continuity sensing through a 8:1 mux
    Restructured schematic so that everything actually fits in page 4
    Updated CubeMX (ioc) file with pinout
2026-06-24 Add peripheral modules
2026-06-24 Finished restructuring schematic
    Most components that were on page 3 are now in their own page
    Added high-frequency 4.7 uF capacitor to servo power line
    Continuity sensing on pyrochannels is multiplexed to one ADC on NAV.
2026-06-24 Finished updating README to reflect all changes to the board
2026-06-24 Began rough component placement
2026-06-25 Update new MCU
2026-06-25 Update README to fix typos/misalignments
2026-06-25 Updated schematic so that servo GND and signal GND are no longer separate
2026-06-25 Continued rough component placement
    Finished most of component placement, only a few passives remain
    Board dimensions basically locked at 155x75 mm
2026-06-26 Completed rough component placement
    Began laying out traces
    Small change to page 12 of schematic (FLASH):
    Connected exposed pad to GND (not sure why I didn't connect it previously)
2026-06-27 Re-annotated schematic
    Continued laying out traces on PCB
2026-06-28 com port flight data, code restructure
2026-06-28 Re-annotated the whole page for no reason
2026-06-28 Did nothing
2026-06-28 Continued laying traces
2026-06-29 random com port loggimg
2026-06-29 Continued laying traces on PCB
2026-06-30 Changed the board to support any telemetry radio
2026-06-30 Updated system architecure diagram and README
2026-06-30 Updated board to support any telemetry radio
    Continued laying traces
